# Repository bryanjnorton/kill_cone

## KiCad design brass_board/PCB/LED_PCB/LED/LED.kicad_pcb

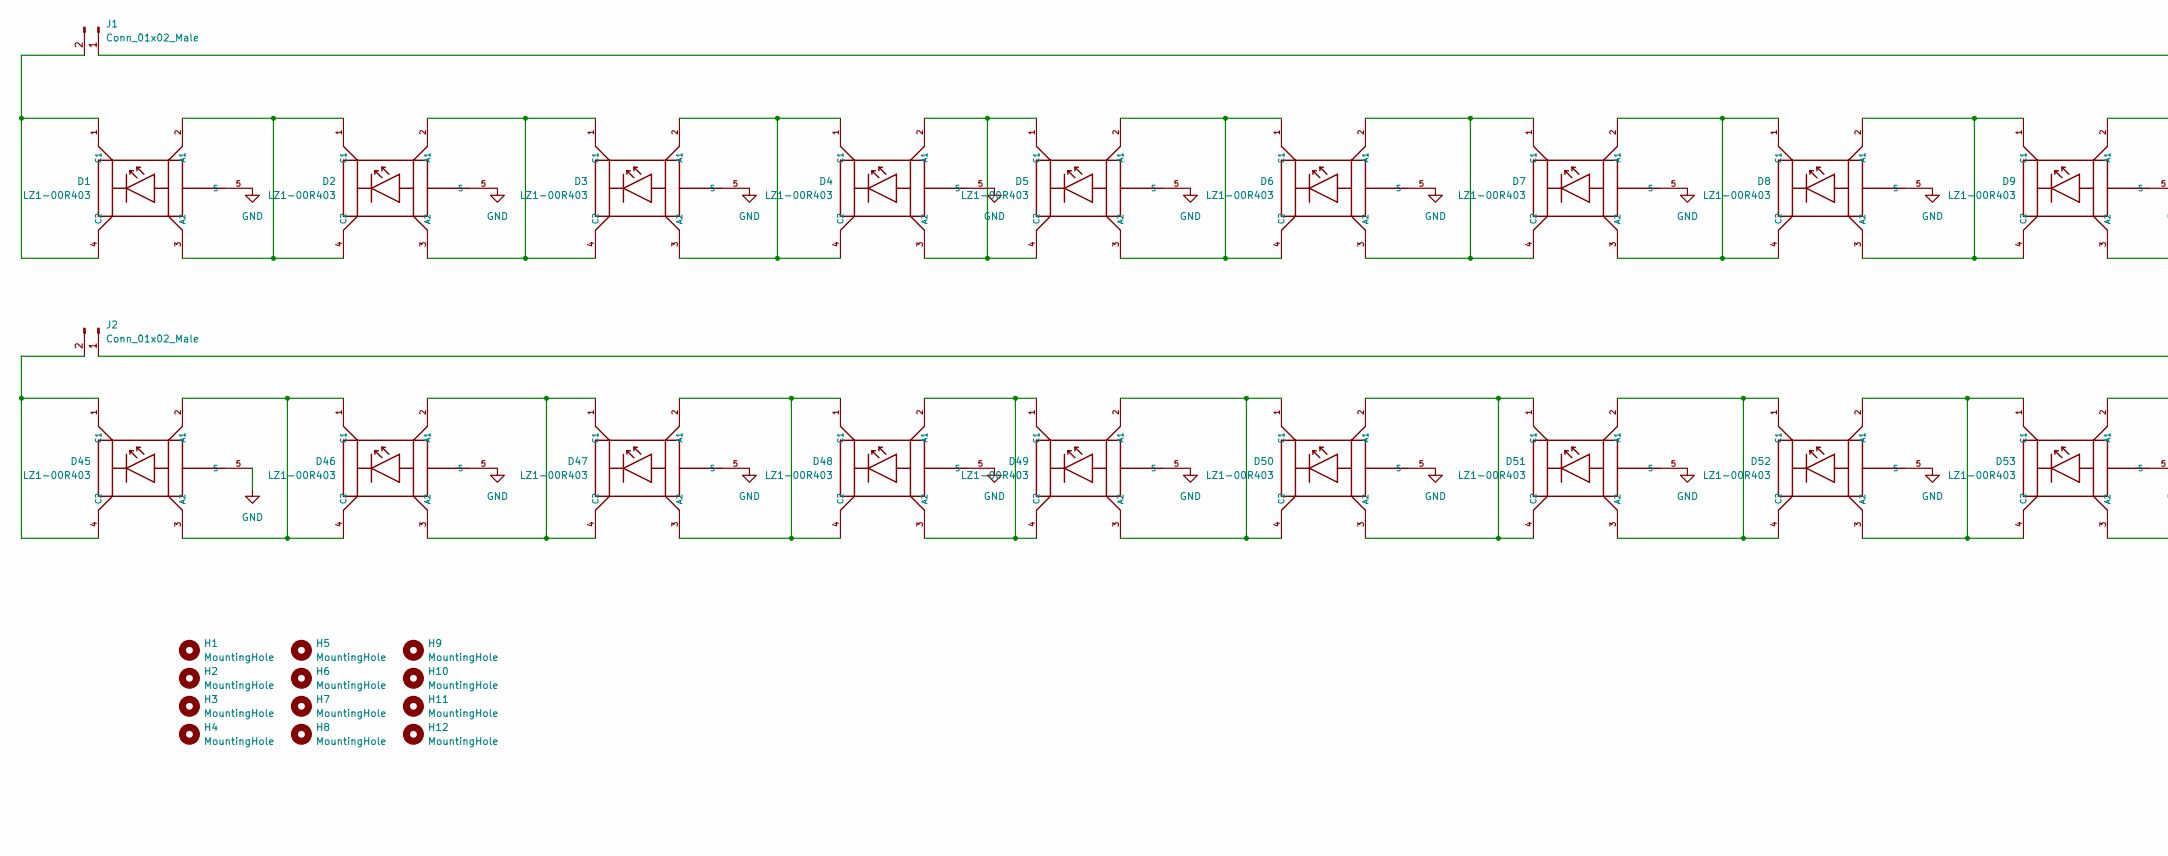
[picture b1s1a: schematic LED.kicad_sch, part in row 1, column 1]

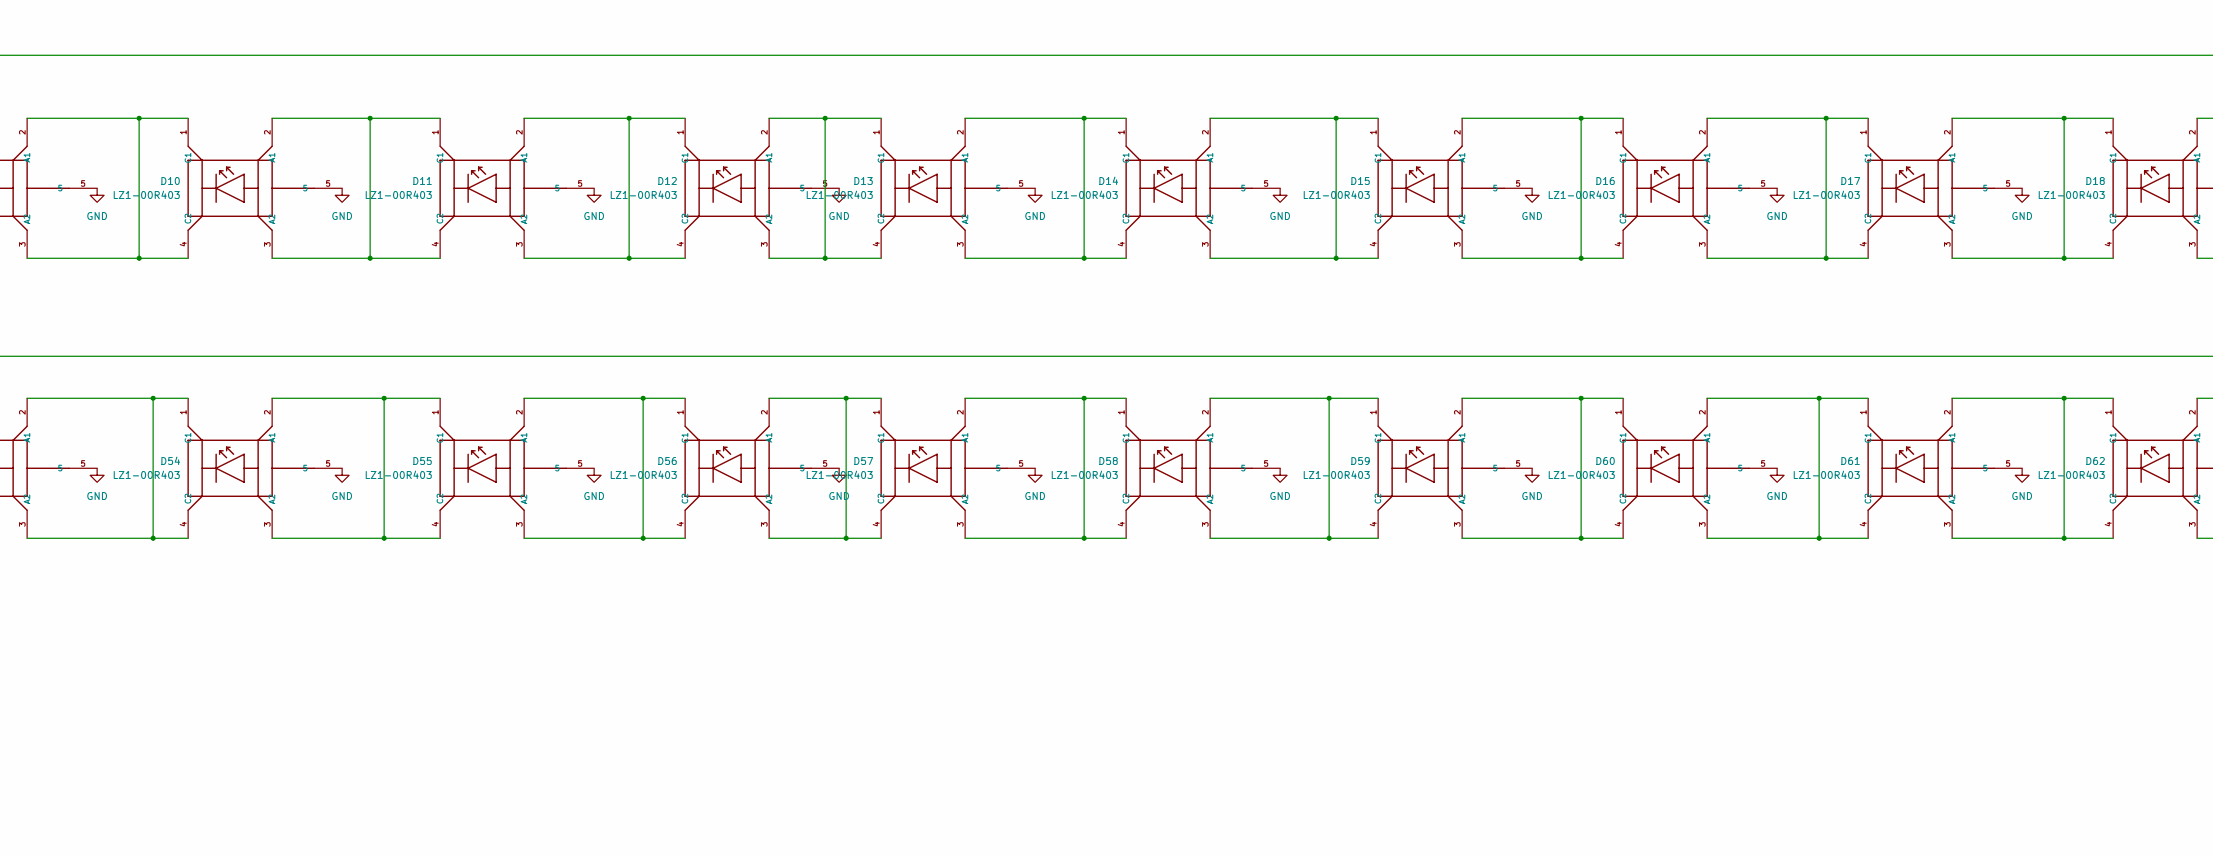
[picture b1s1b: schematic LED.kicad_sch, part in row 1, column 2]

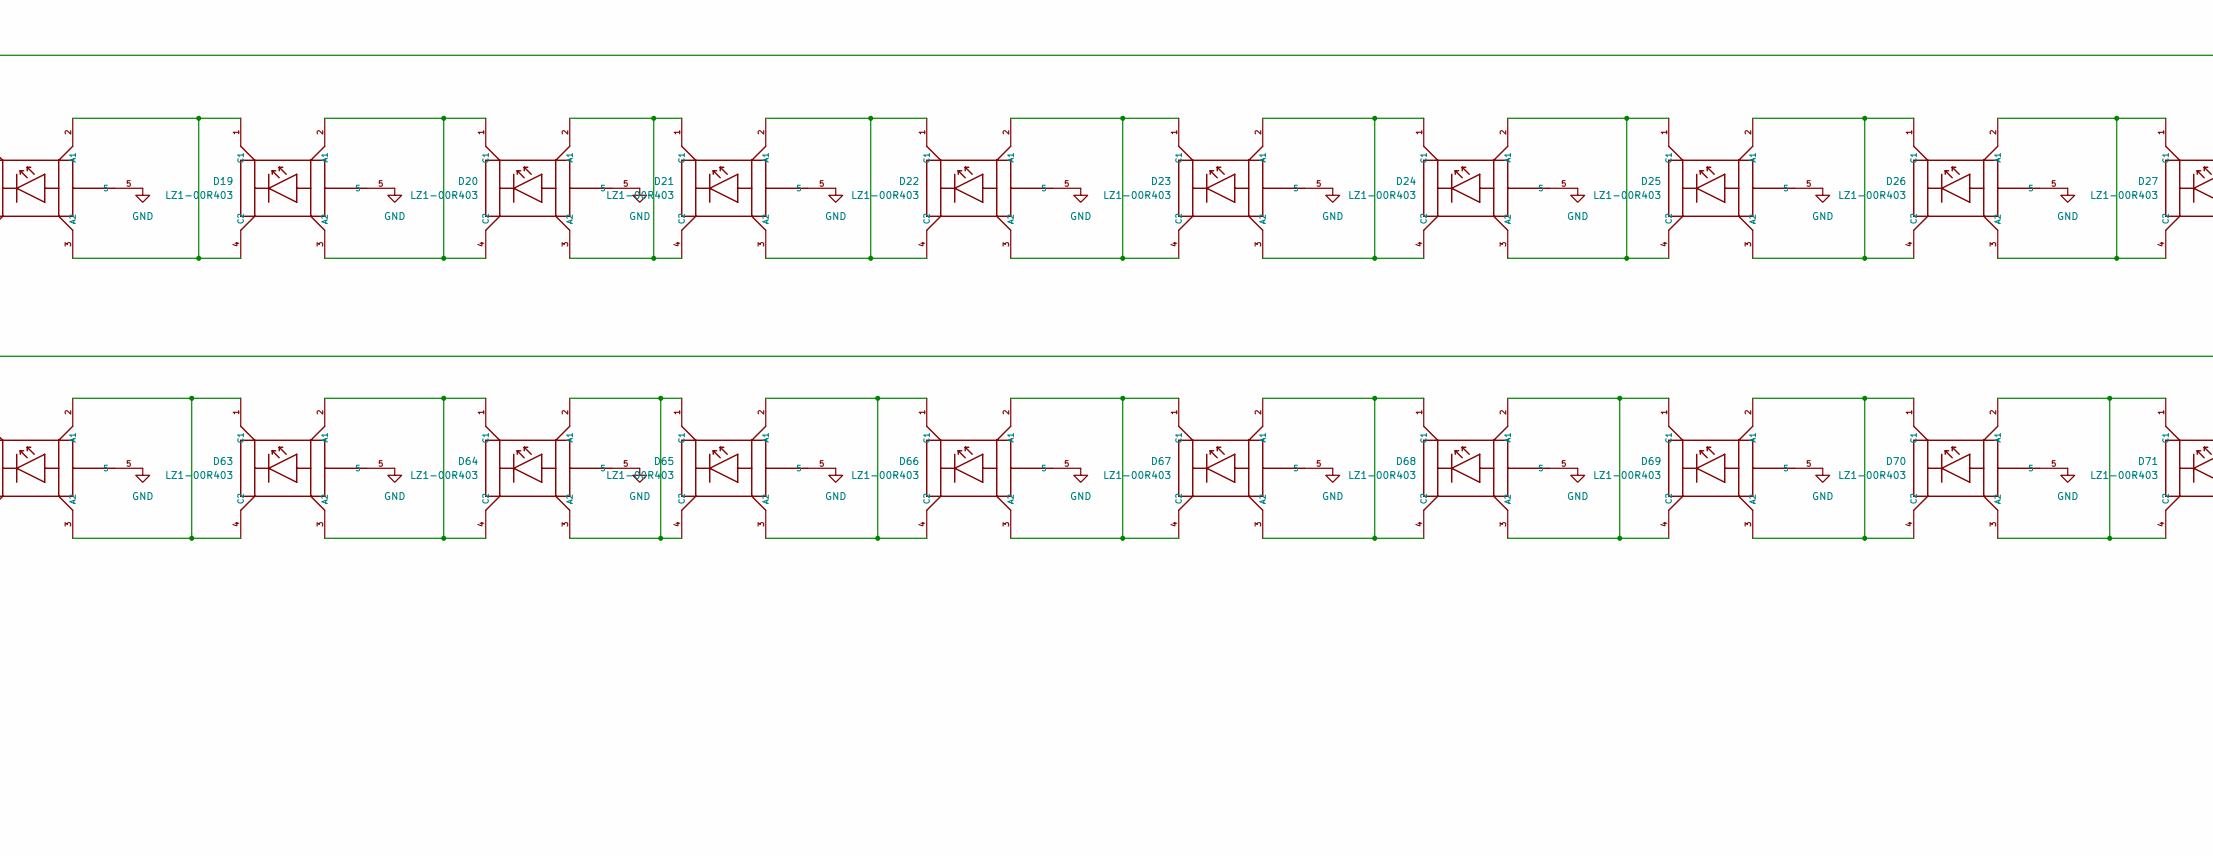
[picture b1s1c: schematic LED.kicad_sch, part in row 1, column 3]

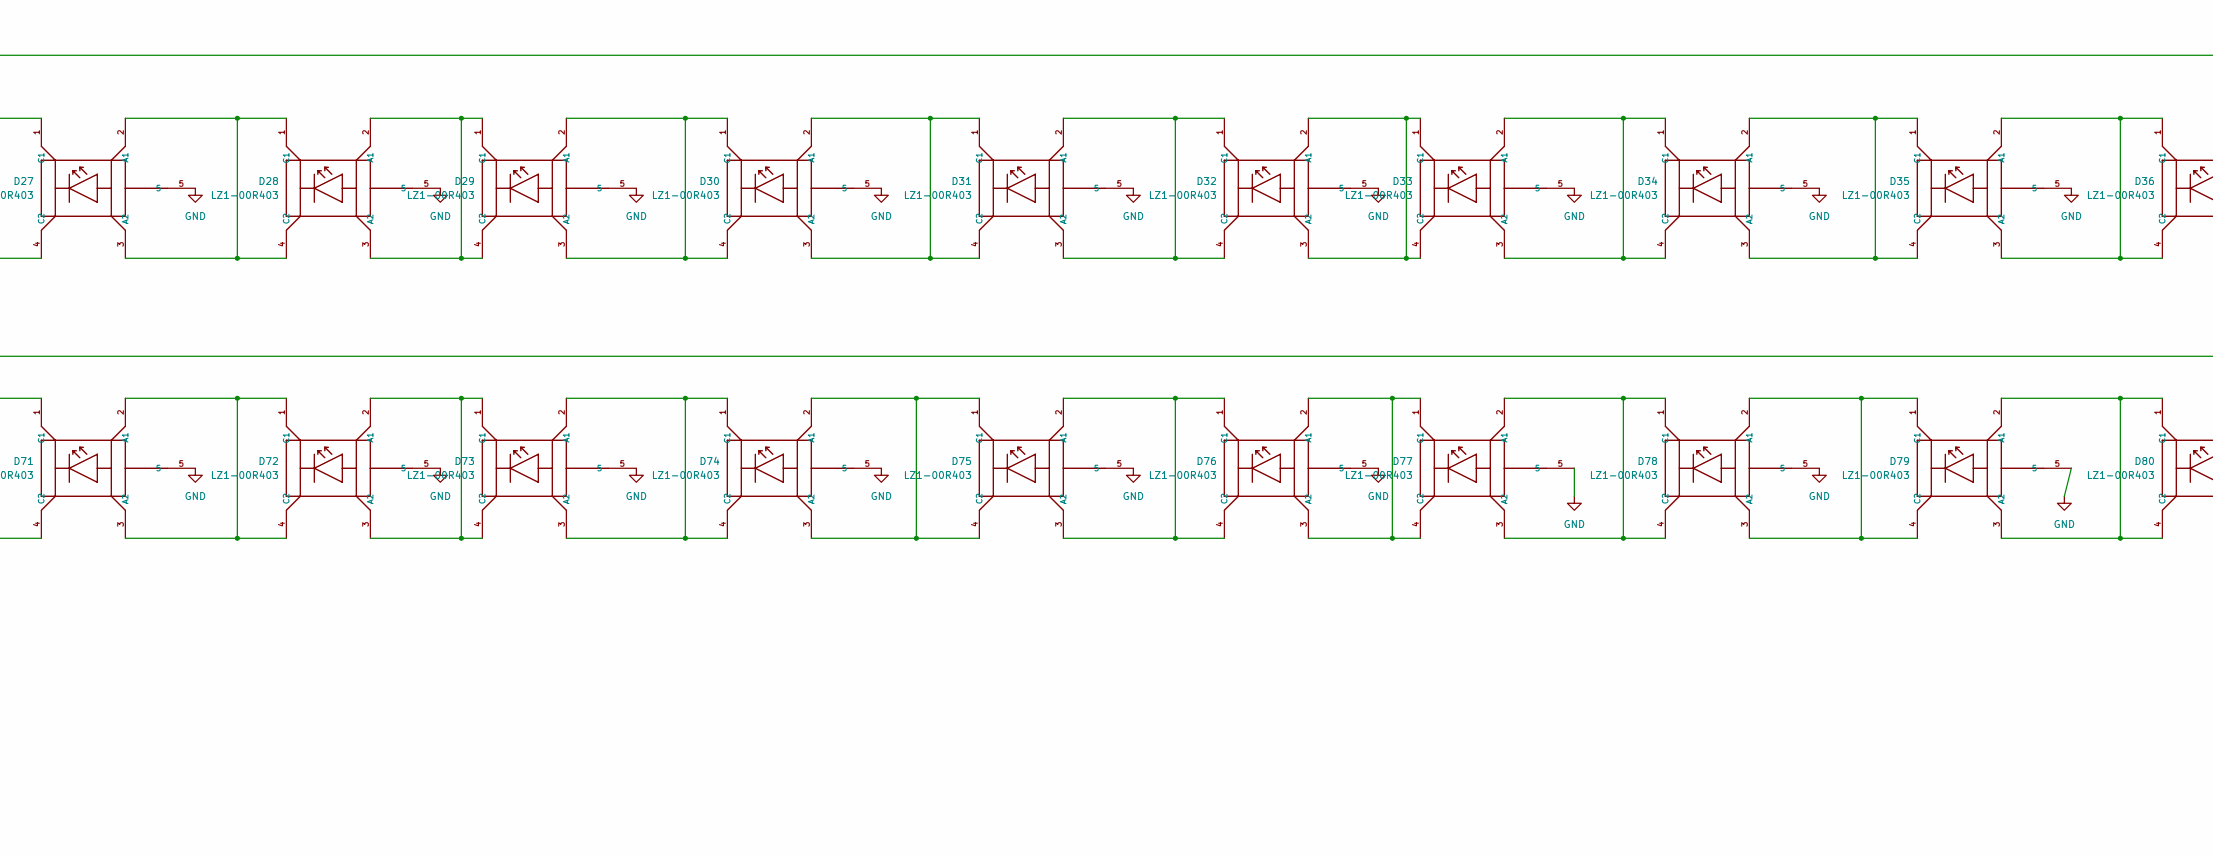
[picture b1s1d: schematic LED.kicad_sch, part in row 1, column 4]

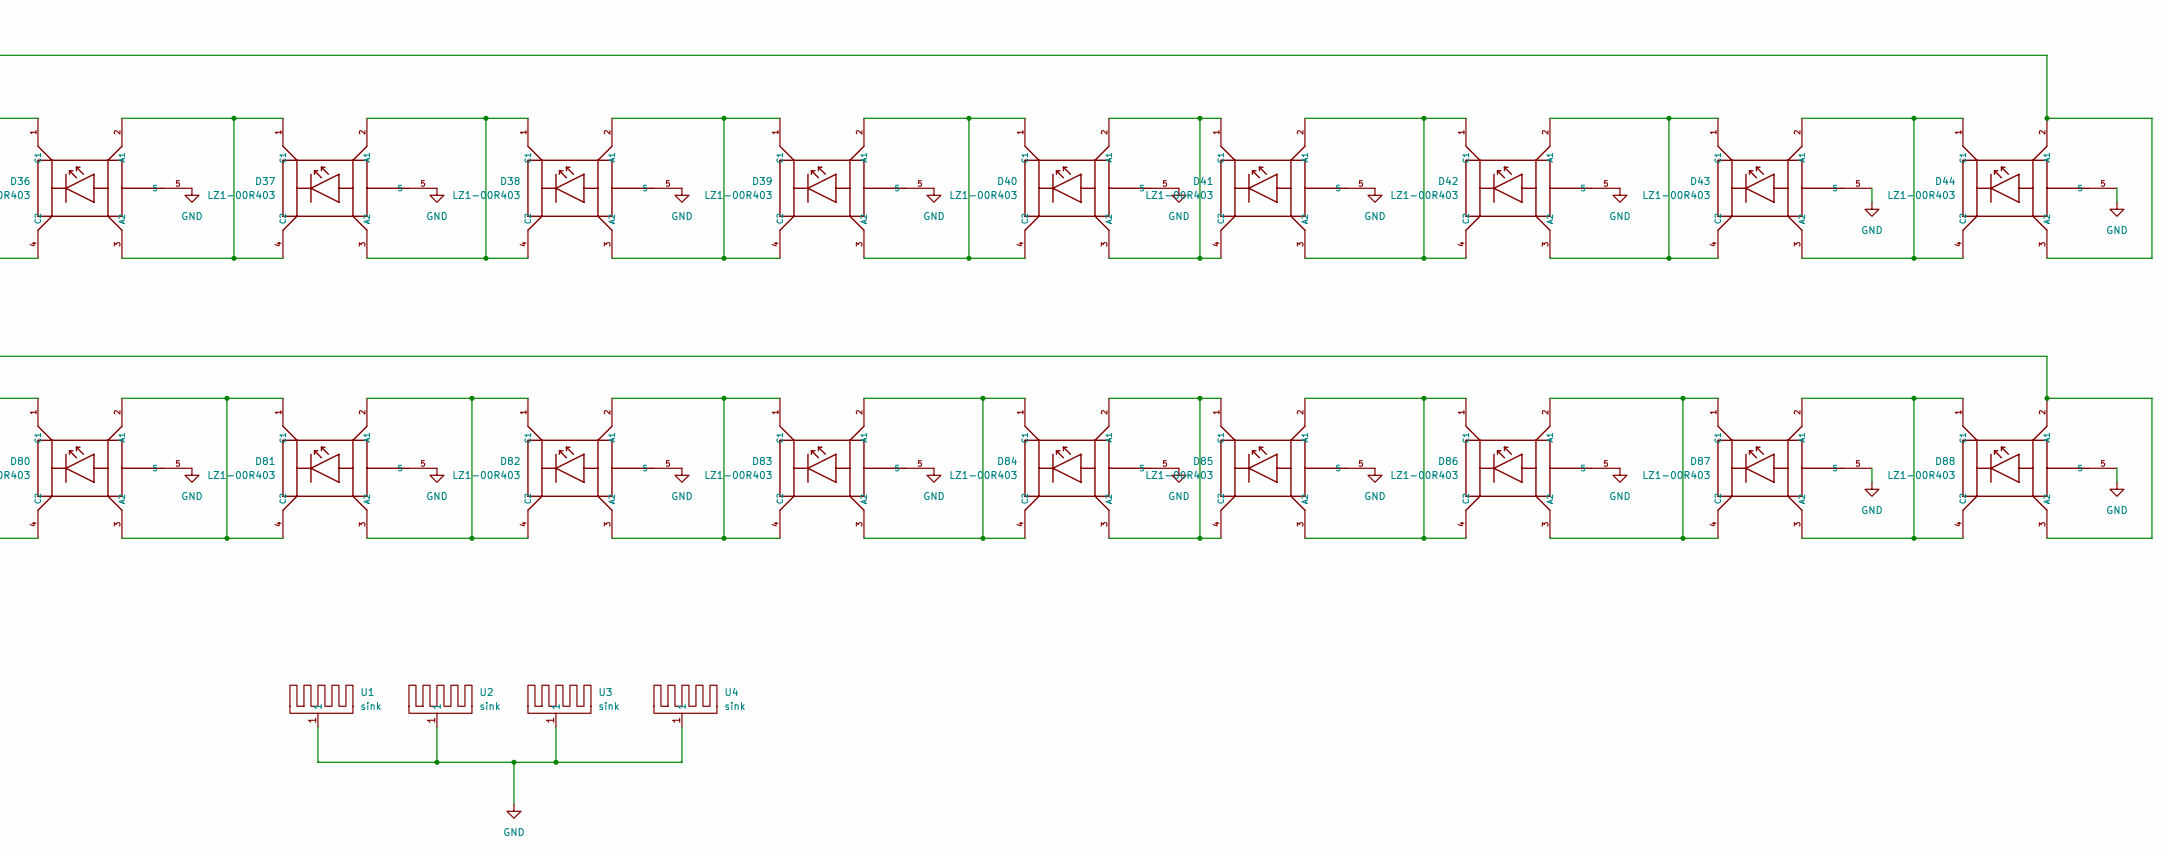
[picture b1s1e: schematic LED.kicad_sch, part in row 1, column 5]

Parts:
D1, D2, D3, D4, D5, D6, D7, D8, D9, D10, D11, D12, D13, D14, D15, D16, D17, D18, D19, D20, D21, D22, D23, D24, D25, D26, D27, D28, D29, D30, D31, D32, D33, D34, D35, D36, D37, D38, D39, D40, D41, D42, D43, D44, D45, D46, D47, D48, D49, D50, D51, D52, D53, D54, D55, D56, D57, D58, D59, D60, D61, D62, D63, D64, D65, D66, D67, D68, D69, D70, D71, D72, D73, D74, D75, D76, D77, D78, D79, D80, D81, D82, D83, D84, D85, D86, D87, D88: LZ1-00R403; LEDSC440X440X240-5N
H1, H2, H3, H4, H5, H6, H7, H8, H9, H10, H11, H12: MountingHole; MountingHole_4.3mm_M4
J1, J2: Conn_01x02_Male; Molex_KK-254_AE-6410-02A_1x02_P2.54mm_Vertical
U1, U2, U3, U4: sink; Heat_Sink

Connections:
GND: D1.5, D2.5, D3.5, D4.5, D5.5, D6.5, D7.5, D8.5, D9.5, D10.5, D11.5, D12.5, D13.5, D14.5, D15.5, D16.5, D17.5, D18.5, D19.5, D20.5, D21.5, D22.5, D23.5, D24.5, D25.5, D26.5, D27.5, D28.5, D29.5, D30.5, D31.5, D32.5, D33.5, D34.5, D35.5, D36.5, D37.5, D38.5, D39.5, D40.5, D41.5, D42.5, D43.5, D44.5, D45.5, D46.5, D47.5, D48.5, D49.5, D50.5, D51.5, D52.5, D53.5, D54.5, D55.5, D56.5, D57.5, D58.5, D59.5, D60.5, D61.5, D62.5, D63.5, D64.5, D65.5, D66.5, D67.5, D68.5, D69.5, D70.5, D71.5, D72.5, D73.5, D74.5, D75.5, D76.5, D77.5, D78.5, D79.5, D80.5, D81.5, D82.5, D83.5, D84.5, D85.5, D86.5, D87.5, D88.5, U1.1, U2.1, U3.1, U4.1
unnamed: D1.1 (C1), D1.4 (C2), J1.2
unnamed: D1.2 (A1), D1.3 (A2), D2.1 (C1), D2.4 (C2)
unnamed: D2.2 (A1), D2.3 (A2), D3.1 (C1), D3.4 (C2)
unnamed: D3.2 (A1), D3.3 (A2), D4.1 (C1), D4.4 (C2)
unnamed: D4.2 (A1), D4.3 (A2), D5.1 (C1), D5.4 (C2)
unnamed: D5.2 (A1), D5.3 (A2), D6.1 (C1), D6.4 (C2)
unnamed: D6.2 (A1), D6.3 (A2), D7.1 (C1), D7.4 (C2)
unnamed: D7.2 (A1), D7.3 (A2), D8.1 (C1), D8.4 (C2)
unnamed: D8.2 (A1), D8.3 (A2), D9.1 (C1), D9.4 (C2)
unnamed: D9.2 (A1), D9.3 (A2), D10.1 (C1), D10.4 (C2)
unnamed: D10.2 (A1), D10.3 (A2), D11.1 (C1), D11.4 (C2)
unnamed: D11.2 (A1), D11.3 (A2), D12.1 (C1), D12.4 (C2)
unnamed: D12.2 (A1), D12.3 (A2), D13.1 (C1), D13.4 (C2)
unnamed: D13.2 (A1), D13.3 (A2), D14.1 (C1), D14.4 (C2)
unnamed: D14.2 (A1), D14.3 (A2), D15.1 (C1), D15.4 (C2)
unnamed: D15.2 (A1), D15.3 (A2), D16.1 (C1), D16.4 (C2)
unnamed: D16.2 (A1), D16.3 (A2), D17.1 (C1), D17.4 (C2)
unnamed: D17.2 (A1), D17.3 (A2), D18.1 (C1), D18.4 (C2)
unnamed: D18.2 (A1), D18.3 (A2), D19.1 (C1), D19.4 (C2)
unnamed: D19.2 (A1), D19.3 (A2), D20.1 (C1), D20.4 (C2)
unnamed: D20.2 (A1), D20.3 (A2), D21.1 (C1), D21.4 (C2)
unnamed: D21.2 (A1), D21.3 (A2), D22.1 (C1), D22.4 (C2)
unnamed: D22.2 (A1), D22.3 (A2), D23.1 (C1), D23.4 (C2)
unnamed: D23.2 (A1), D23.3 (A2), D24.1 (C1), D24.4 (C2)
unnamed: D24.2 (A1), D24.3 (A2), D25.1 (C1), D25.4 (C2)
unnamed: D25.2 (A1), D25.3 (A2), D26.1 (C1), D26.4 (C2)
unnamed: D26.2 (A1), D26.3 (A2), D27.1 (C1), D27.4 (C2)
unnamed: D27.2 (A1), D27.3 (A2), D28.1 (C1), D28.4 (C2)
unnamed: D28.2 (A1), D28.3 (A2), D29.1 (C1), D29.4 (C2)
unnamed: D29.2 (A1), D29.3 (A2), D30.1 (C1), D30.4 (C2)
unnamed: D30.2 (A1), D30.3 (A2), D31.1 (C1), D31.4 (C2)
unnamed: D31.2 (A1), D31.3 (A2), D32.1 (C1), D32.4 (C2)
unnamed: D32.2 (A1), D32.3 (A2), D33.1 (C1), D33.4 (C2)
unnamed: D33.2 (A1), D33.3 (A2), D34.1 (C1), D34.4 (C2)
unnamed: D34.2 (A1), D34.3 (A2), D35.1 (C1), D35.4 (C2)
unnamed: D35.2 (A1), D35.3 (A2), D36.1 (C1), D36.4 (C2)
unnamed: D36.2 (A1), D36.3 (A2), D37.1 (C1), D37.4 (C2)
unnamed: D37.2 (A1), D37.3 (A2), D38.1 (C1), D38.4 (C2)
unnamed: D38.2 (A1), D38.3 (A2), D39.1 (C1), D39.4 (C2)
unnamed: D39.2 (A1), D39.3 (A2), D40.1 (C1), D40.4 (C2)
unnamed: D40.2 (A1), D40.3 (A2), D41.1 (C1), D41.4 (C2)
unnamed: D41.2 (A1), D41.3 (A2), D42.1 (C1), D42.4 (C2)
unnamed: D42.2 (A1), D42.3 (A2), D43.1 (C1), D43.4 (C2)
unnamed: D43.2 (A1), D43.3 (A2), D44.1 (C1), D44.4 (C2)
unnamed: D44.2 (A1), D44.3 (A2), J1.1
unnamed: D45.1 (C1), D45.4 (C2), J2.2
unnamed: D45.2 (A1), D45.3 (A2), D46.1 (C1), D46.4 (C2)
unnamed: D46.2 (A1), D46.3 (A2), D47.1 (C1), D47.4 (C2)
unnamed: D47.2 (A1), D47.3 (A2), D48.1 (C1), D48.4 (C2)
unnamed: D48.2 (A1), D48.3 (A2), D49.1 (C1), D49.4 (C2)
unnamed: D49.2 (A1), D49.3 (A2), D50.1 (C1), D50.4 (C2)
unnamed: D50.2 (A1), D50.3 (A2), D51.1 (C1), D51.4 (C2)
unnamed: D51.2 (A1), D51.3 (A2), D52.1 (C1), D52.4 (C2)
unnamed: D52.2 (A1), D52.3 (A2), D53.1 (C1), D53.4 (C2)
unnamed: D53.2 (A1), D53.3 (A2), D54.1 (C1), D54.4 (C2)
unnamed: D54.2 (A1), D54.3 (A2), D55.1 (C1), D55.4 (C2)
unnamed: D55.2 (A1), D55.3 (A2), D56.1 (C1), D56.4 (C2)
unnamed: D56.2 (A1), D56.3 (A2), D57.1 (C1), D57.4 (C2)
unnamed: D57.2 (A1), D57.3 (A2), D58.1 (C1), D58.4 (C2)
unnamed: D58.2 (A1), D58.3 (A2), D59.1 (C1), D59.4 (C2)
unnamed: D59.2 (A1), D59.3 (A2), D60.1 (C1), D60.4 (C2)
unnamed: D60.2 (A1), D60.3 (A2), D61.1 (C1), D61.4 (C2)
unnamed: D61.2 (A1), D61.3 (A2), D62.1 (C1), D62.4 (C2)
unnamed: D62.2 (A1), D62.3 (A2), D63.1 (C1), D63.4 (C2)
unnamed: D63.2 (A1), D63.3 (A2), D64.1 (C1), D64.4 (C2)
unnamed: D64.2 (A1), D64.3 (A2), D65.1 (C1), D65.4 (C2)
unnamed: D65.2 (A1), D65.3 (A2), D66.1 (C1), D66.4 (C2)
unnamed: D66.2 (A1), D66.3 (A2), D67.1 (C1), D67.4 (C2)
unnamed: D67.2 (A1), D67.3 (A2), D68.1 (C1), D68.4 (C2)
unnamed: D68.2 (A1), D68.3 (A2), D69.1 (C1), D69.4 (C2)
unnamed: D69.2 (A1), D69.3 (A2), D70.1 (C1), D70.4 (C2)
unnamed: D70.2 (A1), D70.3 (A2), D71.1 (C1), D71.4 (C2)
unnamed: D71.2 (A1), D71.3 (A2), D72.1 (C1), D72.4 (C2)
unnamed: D72.2 (A1), D72.3 (A2), D73.1 (C1), D73.4 (C2)
unnamed: D73.2 (A1), D73.3 (A2), D74.1 (C1), D74.4 (C2)
unnamed: D74.2 (A1), D74.3 (A2), D75.1 (C1), D75.4 (C2)
unnamed: D75.2 (A1), D75.3 (A2), D76.1 (C1), D76.4 (C2)
unnamed: D76.2 (A1), D76.3 (A2), D77.1 (C1), D77.4 (C2)
unnamed: D77.2 (A1), D77.3 (A2), D78.1 (C1), D78.4 (C2)
unnamed: D78.2 (A1), D78.3 (A2), D79.1 (C1), D79.4 (C2)
unnamed: D79.2 (A1), D79.3 (A2), D80.1 (C1), D80.4 (C2)
unnamed: D80.2 (A1), D80.3 (A2), D81.1 (C1), D81.4 (C2)
unnamed: D81.2 (A1), D81.3 (A2), D82.1 (C1), D82.4 (C2)
unnamed: D82.2 (A1), D82.3 (A2), D83.1 (C1), D83.4 (C2)
unnamed: D83.2 (A1), D83.3 (A2), D84.1 (C1), D84.4 (C2)
unnamed: D84.2 (A1), D84.3 (A2), D85.1 (C1), D85.4 (C2)
unnamed: D85.2 (A1), D85.3 (A2), D86.1 (C1), D86.4 (C2)
unnamed: D86.2 (A1), D86.3 (A2), D87.1 (C1), D87.4 (C2)
unnamed: D87.2 (A1), D87.3 (A2), D88.1 (C1), D88.4 (C2)
unnamed: D88.2 (A1), D88.3 (A2), J2.1

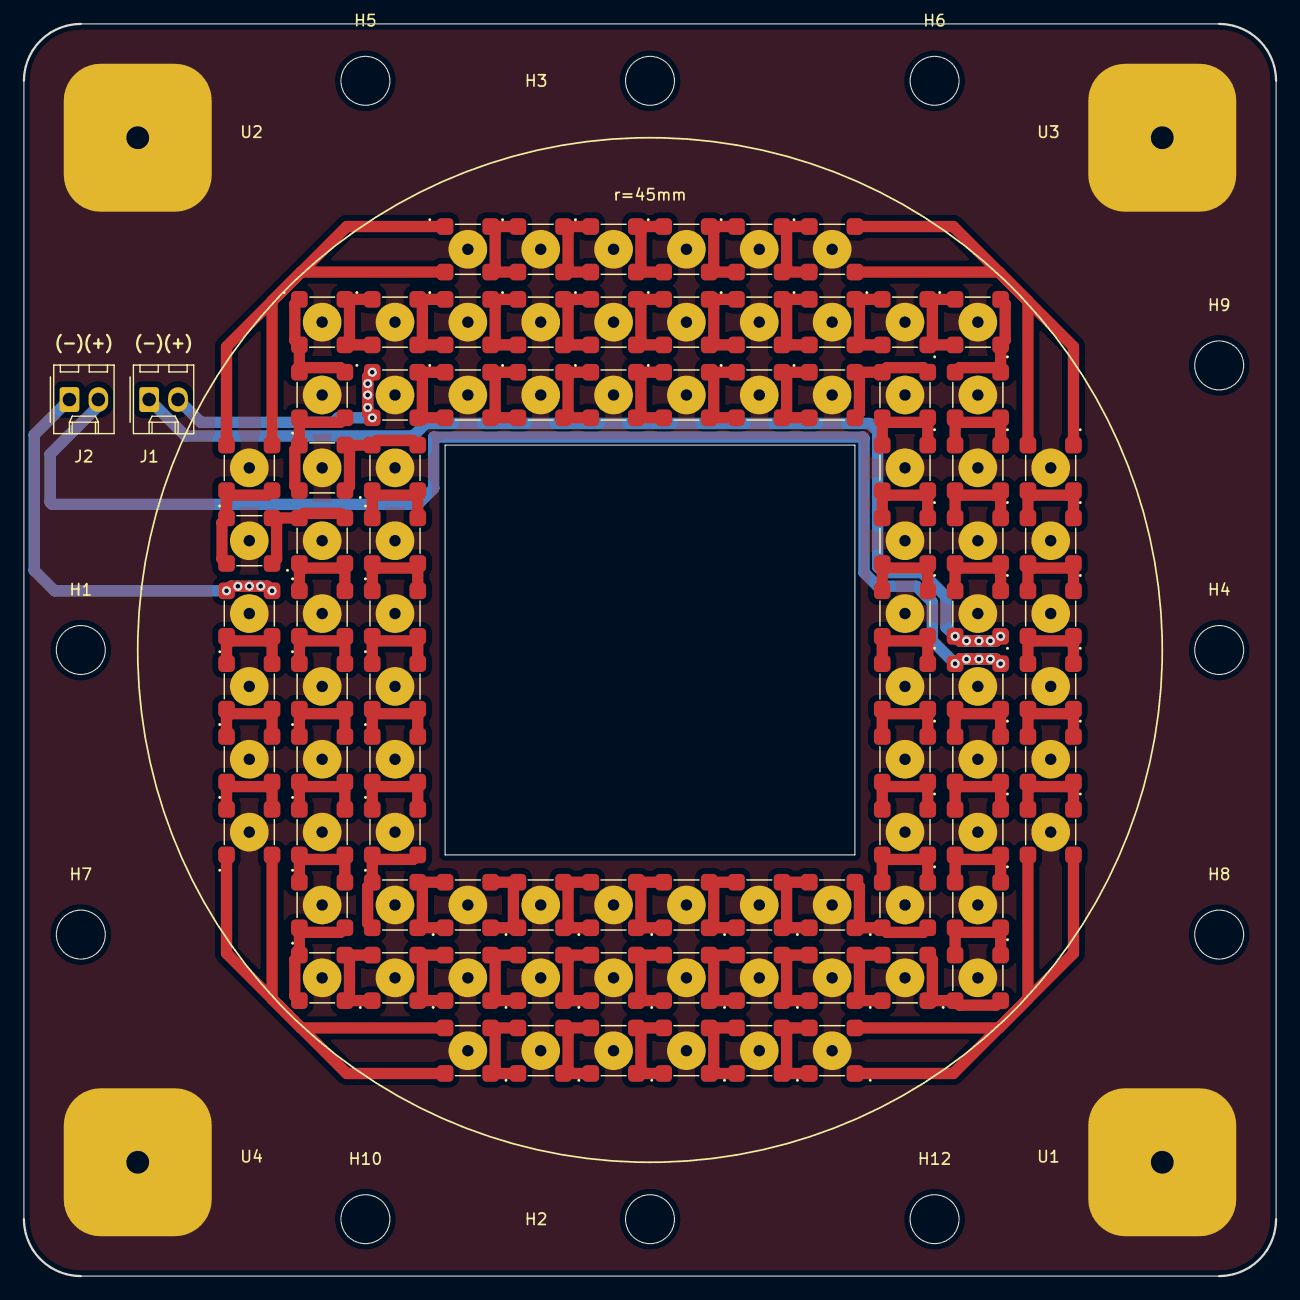
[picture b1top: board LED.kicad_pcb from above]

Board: 2 copper layers, 110.0 x 110.0 mm, 106 parts (0 on the bottom side), 91 nets.

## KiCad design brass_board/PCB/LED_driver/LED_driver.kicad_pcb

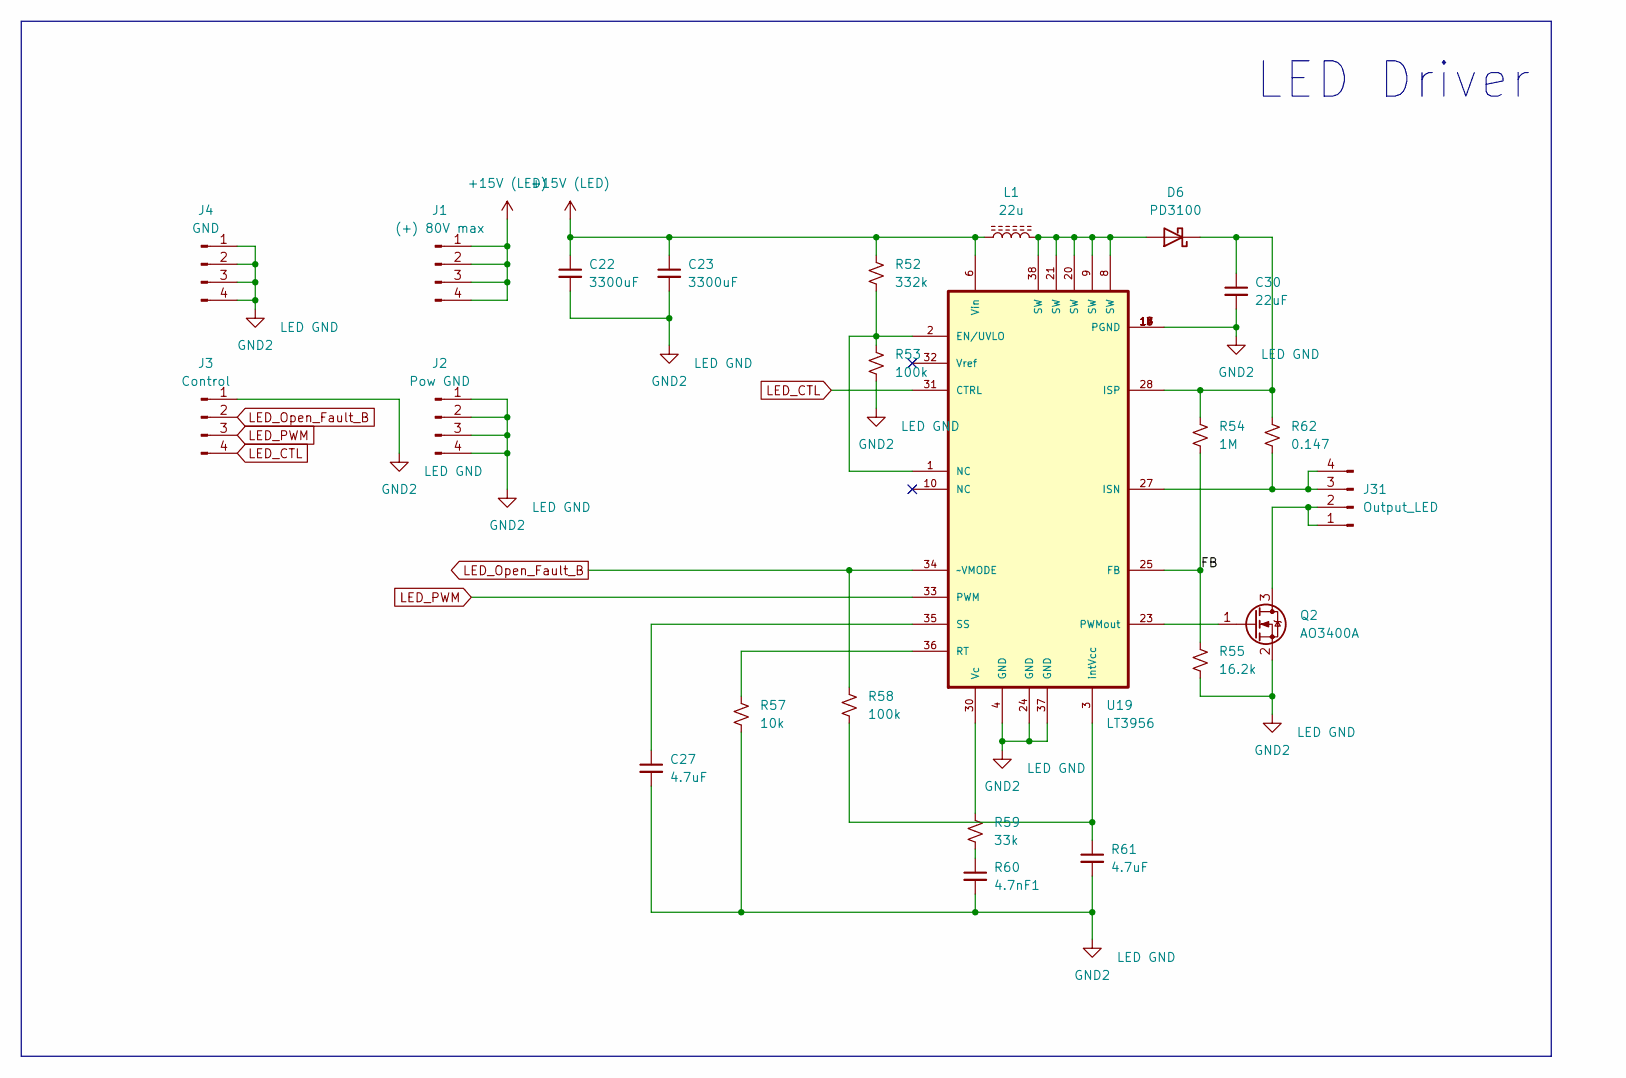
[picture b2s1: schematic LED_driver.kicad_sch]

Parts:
C22, C23: 3300uF; CP_Elec_18x22
C27: 4.7uF; C_0603_1608Metric
C30: 22uF; C_2220_5650Metric; LCSC C575373
D6: PD3100; D_SMA
J1: (+) 80V max; PinHeader_1x04_P2.54mm_Vertical
J2: Pow GND; PinHeader_1x04_P2.54mm_Vertical
J3: Control; PinHeader_1x04_P2.54mm_Vertical
J4: GND; PinHeader_1x04_P2.54mm_Vertical
J31: Output_LED; Molex_KK-254_AE-6410-04A_1x04_P2.54mm_Vertical; LCSC C124378
L1: 22u; CDRH74; LCSC C133406
Q2: AO3400A; SOT-23
R52: 332k; C_0603_1608Metric
R53, R58: 100k; C_0603_1608Metric
R54: 1M; C_0603_1608Metric
R55: 16.2k; C_0603_1608Metric
R57: 10k; C_0603_1608Metric
R59: 33k; C_0603_1608Metric
R60: 4.7nF1; C_0603_1608Metric
R61: 4.7uF; C_0603_1608Metric
R62: 0.147; R_1206_3216Metric; LCSC C407311
U19: LT3956; CONV_LT3958EUHE#PBF

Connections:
+15V: C22.1, C23.1, J1.1, J1.2, J1.3, J1.4, L1.1, R52.1, U19.6 (Vin)
/FB: R54.2, R55.1, U19.25 (FB)
GND2: C22.2, C23.2, C27.2, C30.2, J2.1, J2.2, J2.3, J2.4, J3.1, J4.1, J4.2, J4.3, J4.4, Q2.2 (S), R53.2, R55.2, R57.2, R60.2, R61.2, U19.4 (GND), U19.12 (PGND), U19.13 (PGND), U19.14 (PGND), U19.15 (PGND), U19.16 (PGND), U19.17 (PGND), U19.24 (GND), U19.37 (GND)
LED_CTL: J3.4, U19.31 (CTRL)
LED_Open_Fault_B: J3.2, R58.1, U19.34 (~VMODE)
LED_PWM: J3.3, U19.33 (PWM)
unnamed: C27.1, U19.35 (SS)
unnamed: C30.1, D6.1 (K), R54.1, R62.1, U19.28 (ISP)
unnamed: D6.2 (A), L1.2, U19.8 (SW), U19.9 (SW), U19.20 (SW), U19.21 (SW), U19.38 (SW)
unnamed: J31.1, J31.2, Q2.3 (D)
unnamed: J31.3, J31.4, R62.2, U19.27 (ISN)
unnamed: Q2.1 (G), U19.23 (PWMout)
unnamed: R57.1, U19.36 (RT)
unnamed: R58.2, R61.1, U19.3 (intVcc)
unnamed: R59.1, U19.30 (Vc)
unnamed: R59.2, R60.1
unnamed: R52.2, R53.1, U19.1 (NC), U19.2 (EN/UVLO)

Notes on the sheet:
LED Driver

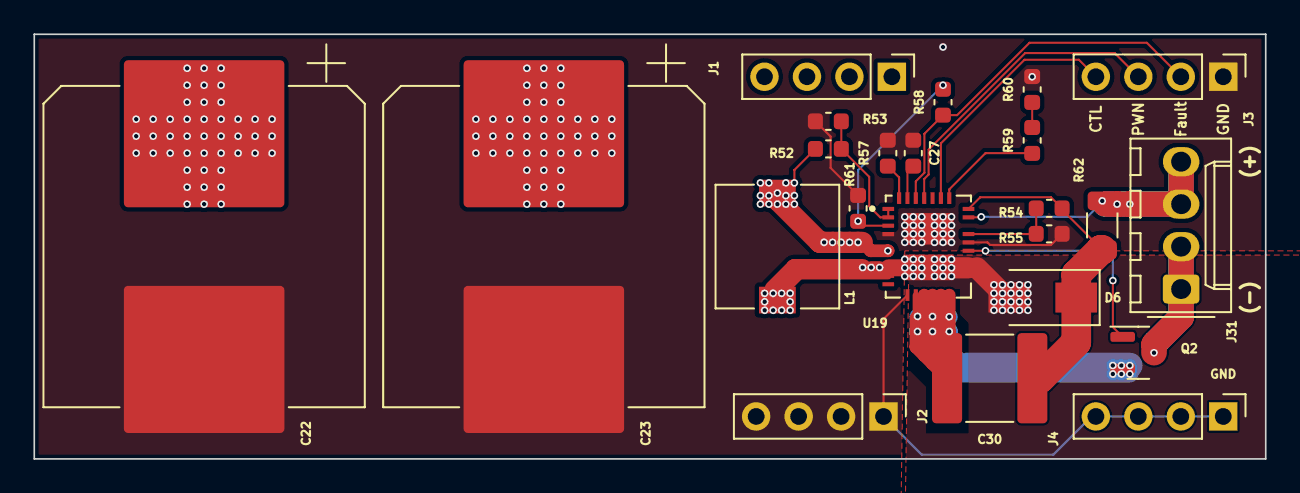
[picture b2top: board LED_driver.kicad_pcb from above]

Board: 2 copper layers, 73.7 x 25.4 mm, 23 parts (0 on the bottom side), 17 nets.
